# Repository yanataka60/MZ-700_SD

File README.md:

# MZ-700バンク切替対応MZ-80K_SD基板

　MZ-80K_SDはROMをF000Hに置くことでFDコマンドを利用してフロッピーディスク装置の代わりにSD-CARDを繋いでしまおうというものですが、MZ-700でバンク切替によりオールRAMとなったときに、MZ-80K_SDのROMがEnableのままなのでMZ-700本体のRAMと両方有効になってしまっています。

　実際にS-BASIC等動かしてみるとそのまま問題なく動いているようにも見えるのですが、バンクが切り替わったときにはROMがDisableになったほうが安心です。

　MZ-700_SDではバンクが切り替わったときにGAL16V8を使ってROMのDisable、Enableが自動で切り替わります。

#### 試作から2か月経過しましたが、特に問題が発生していないので正式公開とします。

~~####  ただし、MZ-80K_SD開発時に使っていたGAL22V10がMZ-80K本体と相性が悪いのかどうにも動作が不安定で泣く泣く汎用ロジックICに置き換えた経験からGALを使っても動作が安定していると確信できるまではテスト公開とします。~~

####  また、入手性も汎用ロジックICに比べてGAL16V8は良くないです。

　なお、GAL16V8、Arduino、ROMへ書き込むための機器が別途必要となります。

#### 2024.10.10 MZ-80K_SD基板をRev1.5.5とし、ROMを切り離しスイッチを標準装備としました。

　MZ-80K_SDのページではスイッチでROMを切り離すMZ-80K_SD Rev1.5.5基板を公開しています。

https://github.com/yanataka60/MZ80K_SD

　Rev1.5.3基板でROMを切り離すスイッチを付ける方法はこちらです。

https://github.com/yanataka60/MZ80K_SD?tab=readme-ov-file#rom%E5%88%87%E3%82%8A%E9%9B%A2%E3%81%97%E3%82%B9%E3%82%A4%E3%83%83%E3%83%81%E6%94%B9%E9%80%A0

### (2026.8.13追記)すねいるさんのBARYONに対応するためArduinoプログラムを更新しました。また、ROMプログラムも合わせて更新することで多段ロードにも対応します。

### 多段ロードの詳細についてはMZ-80K_SDの「BARYON対応」「多段ロード対応」を参照してください。

BARYON対応:https://github.com/yanataka60/MZ80K_SD#baryon%E5%AF%BE%E5%BF%9C2026813

多段ロード対応:https://github.com/yanataka60/MZ80K_SD#%E5%A4%9A%E6%AE%B5%E3%83%AD%E3%83%BC%E3%83%89%E5%AF%BE%E5%BF%9C2026813

　Arduinoプログラム、ROMプログラムともMZ-80K_SD用に更新したものがそのまま使えます。

## 回路図
　KiCadフォルダ内のMZ-700_SD.pdf参照

[回路図](https://github.com/yanataka60/MZ-700_SD/blob/main/KiCad/MZ700_SD.pdf)

## 部品
　U7 GAL16V8 1個が追加された以外はMZ-80K_SD Rev1.5.3と同様です。

　MZ-80K_SD Rev1.5.5との違いはRev1.5.5でのS3スイッチと10kΩの抵抗の代わりにGAL16V8が必要となります。

　私はGAL16V8Dを使っています。

|番号|品名|数量|備考|
| ------------ | ------------ | ------------ | ------------ |
|U1|74LS04|1||
|U2|2764又は28C64|1|ROMの相性については後述|
|U3|8255|1||
|U4|Arduino_Pro_Mini_5V|1|Atmega328版を使用 168版は不可。(注1)|
|U5 U6|74LS30|2||
|U7|GAL16V8|1||
||J2、J5のいづれか|||
|J2|Micro SD Card Kit又は同等品|1|秋月電子通商 AE-microSD-LLCNV (注2) (注3)|
|J5|MicroSD Card Adapter|1|Arduino等に使われる5V電源に対応したもの (注3)|
|C1-C5,C7|積層セラミックコンデンサ 0.1uF|6||
|C6|電解コンデンサ 16v100uF|1||
|S1 S2|3Pスライドスイッチ|2|秋月電子通商 SS12D01G4など|
|J4|DCジャック|1||
|J3|コネクタ 2Pin|1|ピンヘッダで代用するときはGNDと間違えないよう1Pinで5Vだけにしたほうが良い|
|J1|50Pinコネクタ|1||
||50Pinケーブル|1||
||ピンヘッダ|2Pin分|Arduino_Pro_MiniにはA4、A5用のピンヘッダが付いていないため別途調達が必要です 秋月電子通商 PH-1x40SGなど|
||本体内から5Vを取る場合、ケーブル少々|||
||本体ROMにパッチをあてる場合、27C32等を2532ソケットに差すためのアダプタ|||
||ピンソケット(任意)|26Pin分|Arduino_Pro_Miniを取り外し可能としたい場合に調達します 秋月電子通商 FHU-1x42SGなど|

　　　注1)Arduino Pro MiniはA4、A5ピンも使っています。

　　　注2)秋月電子通商　AE-microSD-LLCNVのJ1ジャンパはショートしてください。

　　　注3)J2又はJ5のどちらかを選択して取り付けてください。

### MicroSD Card Adapterを使う(Rev1.5.3以降)
J5に取り付けます。

MicroSD Card Adapterについているピンヘッダを除去してハンダ付けするのが一番確実ですが、J5の穴にMicroSD Card Adapterをぴったりと押しつけ、裏から多めにハンダを流し込むことでハンダ付けをする方法もあります。なお、この方法の時にはしっかりハンダ付けが出来たかテスターで導通を確認しておいた方が安心です。

ハンダ付けに自信のない方はJ2の秋月電子通商　AE-microSD-LLCNVをお使いください。AE-microSD-LLCNVならパワーLED、アクセスLEDが付いています。

.JPG)

.JPG)

.JPG)

.JPG)

## GAL16V8プログラム
　Wincuplフォルダ内のMZ700_ROM.jedをROMライター(TL866II Plus等)を使ってGAL16V8に書き込んでください。

## ROMプログラムについて、Arduinoプログラム等
　以下、MZ-80K_SD Rev1.5.5と同様ですのでMZ-80K_SDプロジェクトを参照してください。。

https://github.com/yanataka60/MZ80K_SD?tab=readme-ov-file#rom%E3%83%97%E3%83%AD%E3%82%B0%E3%83%A9%E3%83%A0%E3%81%AB%E3%81%A4%E3%81%84%E3%81%A6

## テストプログラム
　RAMへの書込みが正常に行われ、読み出す時にはROMのデータと混じらずに書き込んだデータと同じ値が正常に読み出せること、またROMを読み出してもデータが不変であることを確認するためにテストプログラムを作成しました。

　Z80フォルダTESTフォルダ内のTEST-MZ700.MZTを実行するとROMを読出して比較、RAMに書込み、読出して比較をバンク切替しながらF000hからFFFFhまでのメモリアドレスを順次検査していき、RAMの読出し比較がエラーとなればそこで止まります。

　私の環境でバンク切替対応基板が正常に終了することは確認済みですが、困ったことに未対策のMZ-80K_SD Rev1.5.3基板でも正常に終了してしまいました。

　MZ-80Kではスタートと同時にエラーで止まりますのでテストプログラムは正常なはずです。

　ROMとRAMのアクセスタイムが関係しているのかもしれませんが、バンク切替対応基板だとここが直りますというところが明確ではないです。

　なお、ロジックアナライザを使い、バンク切替対応基板ではOUT (E1h),AでGAL16V8 Pin17(LATCH)がDisableとなり、OUT (E3h),A、OUT (E4h),AでGAL16V8 Pin17(LATCH)がEnableとなり正常に動作することは確認しています。

　　未対策のMZ-80K_SD Rev1.5.3基板ではOUT (E1h),A、OUT (E3h),A、OUT (E4h),Aいずれの状態でもF000h～FFFFhアクセス時にROMCEはEnableのままです。

## EMMボード for MZ-700からの起動
　拙作EMMボード for MZ-700をバッテリーバックアップに対応させたのでEMM_for_MZ-700から起動するコマンドを追加してみました。

　https://github.com/yanataka60/EMM_for_MZ-700

　コマンド「FDE0」～「FDE3」を使うことで「EMM0」～「EMM3」のHuBASICから起動させることが出来ます。

　なお、EMMの00000番地が「01h」でなければEMMからの起動はせずにコマンド待ちに戻りますが、00000番地以降に異常があってもチェックはしていないので最悪暴走します。

　MZ-700用HuBASICはテープ版しかなくそのままではEMMにHuBASICの起動イメージを作成することが出来ません。

　BouKiCHiさんのHuDiskなどを使いMZ-700用HuBASICの起動ディスクイメージを作成したうえでEMMMENUのEMMLOADでEMMに書き込む必要があります。

### ROMに書き込む
~~EMMフォルダ内のFD_rom.BINをROMライター(TL866II Plus等)を使って2764に書き込んでください。~~

(2026.8.13)多段ロード対応に伴い、MZ-80K_SDに統合しました。MZ-80K_SD/Z80フォルダ内のFD_rom.BINを使ってください。

## 謝辞
　基板の作成に当たり以下のデータを使わせていただきました。ありがとうございました。

　Arduino Pro Mini

　　https://github.com/g200kg/kicad-lib-arduino

　AE-microSD-LLCNV

　　https://github.com/kuninet/PC-8001-SD-8kRAM

## 追記
2024.10.10 正式公開

2025.12.4 kuran_kuranさんにArduinoプログラムのバグを発見していただきました。精査した結果、不要な処理が含まれていることが原因であったため不要な処理部分を削除しました。なお、未修正のままでも実害はありません。kuran_kuranさん、ありがとうございました。

2026.1.23 EMMサポートプログラムを追加。

2026.8.13 BARYONに対応しました。retrogamer128さんの要望により多段ロードに対応しました。

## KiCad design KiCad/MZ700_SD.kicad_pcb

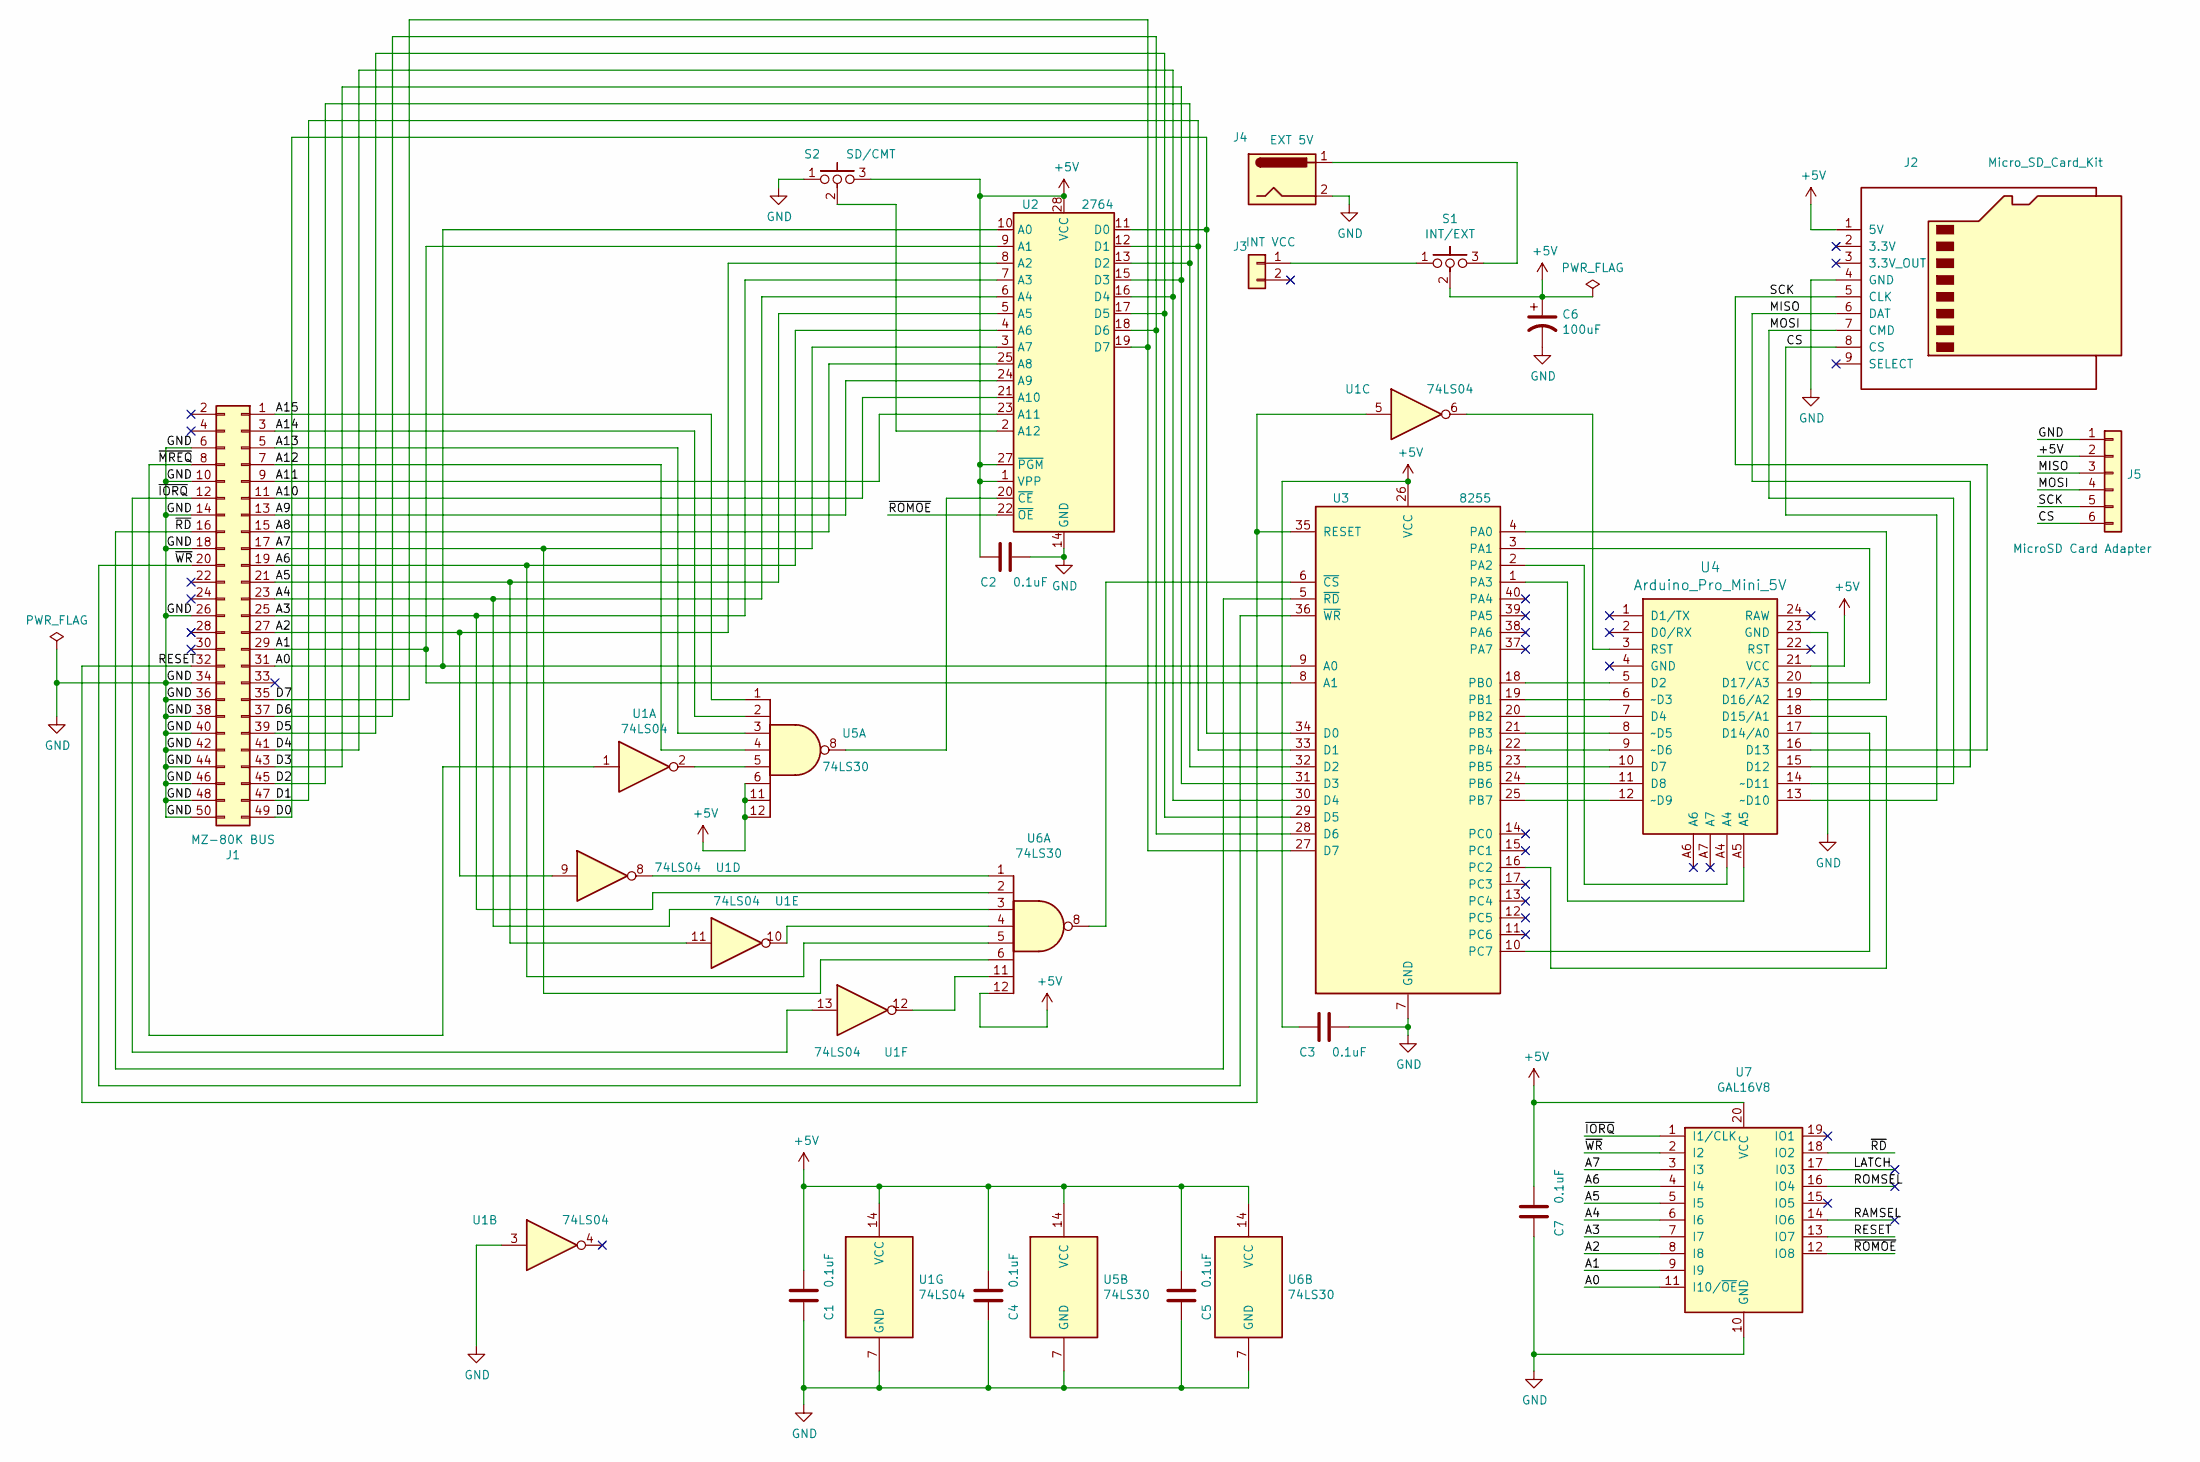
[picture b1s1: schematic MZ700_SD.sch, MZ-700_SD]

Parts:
C1, C2, C3, C4, C5, C7: 0.1uF; C_Rect_L4.0mm_W2.5mm_P2.50mm
C6: 100uF; CP_Radial_D5.0mm_P2.50mm
J1: MZ-80K BUS; PinSocket_2x25_P2.54mm_Horizontal
J2: Micro_SD_Card_Kit; AE-microSD-LLCNV
J3: INT VCC; PinHeader_1x02_P2.54mm_Horizontal
J4: EXT 5V; BarrelJack_Horizontal
J5: MicroSD Card Adapter; PinSocket_1x06_P2.54mm_Vertical
S1: INT/EXT; PinHeader_1x03_P2.54mm_Vertical
S2: SD/CMT; PinHeader_1x03_P2.54mm_Vertical
U1: 74LS04; DIP-14_W7.62mm_LongPads
U2: 2764; DIP-28_W15.24mm_LongPads
U3: 8255; DIP-40_W15.24mm_LongPads
U4: Arduino_Pro_Mini_5V; Arduino_Pro_Mini
U5, U6: 74LS30; DIP-14_W7.62mm_LongPads
U7: GAL16V8; DIP-20_W7.62mm_LongPads

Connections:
+5V: C1.2, C2.1, C3.1, C4.2, C5.2, C6.1, C7.2, J2.1 (5V), J5.2, S1.2, S2.3, U1.14 (VCC), U2.1 (VPP), U2.27 (~PGM), U2.28 (VCC), U3.26 (VCC), U4.21 (VCC), U5.6, U5.11, U5.12, U5.14 (VCC), U6.12, U6.14 (VCC), U7.20 (VCC)
/A0: J1.31, U2.10 (A0), U3.9 (A0), U7.11 (I10/~OE~)
/A1: J1.29, U2.9 (A1), U3.8 (A1), U7.9 (I9)
/A2: J1.27, U1.9, U2.8 (A2), U7.8 (I8)
/A3: J1.25, U2.7 (A3), U6.2, U7.7 (I7)
/A4: J1.23, U2.6 (A4), U6.3, U7.6 (I6)
/A5: J1.21, U1.11, U2.5 (A5), U7.5 (I5)
/A6: J1.19, U2.4 (A6), U6.5, U7.4 (I4)
/A7: J1.17, U2.3 (A7), U6.6, U7.3 (I3)
/A8: J1.15, U2.25 (A8)
/A9: J1.13, U2.24 (A9)
/A10: J1.11, U2.21 (A10)
/A11: J1.9, U2.23 (A11)
/A12: J1.7, U5.4
/A13: J1.5, U5.3
/A14: J1.3, U5.2
/A15: J1.1, U5.1
/CS: J2.8 (CS), J5.6, U4.13 (~~D10)
/D0: J1.49, U2.11 (D0), U3.34 (D0)
/D1: J1.47, U2.12 (D1), U3.33 (D1)
/D2: J1.45, U2.13 (D2), U3.32 (D2)
/D3: J1.43, U2.15 (D3), U3.31 (D3)
/D4: J1.41, U2.16 (D4), U3.30 (D4)
/D5: J1.39, U2.17 (D5), U3.29 (D5)
/D6: J1.37, U2.18 (D6), U3.28 (D6)
/D7: J1.35, U2.19 (D7), U3.27 (D7)
/MISO: J2.6 (DAT), J5.3, U4.15 (D12)
/MOSI: J2.7 (CMD), J5.4, U4.14 (~~D11)
/RESET: J1.32, U1.5, U3.35 (RESET), U7.13 (IO7)
/SCK: J2.5 (CLK), J5.5, U4.16 (D13)
/~IORQ: J1.12, U1.13, U7.1 (I1/CLK)
/~MREQ: J1.8, U1.1
/~RD: J1.16, U3.5 (~RD~), U7.18 (IO2)
/~ROMOE: U2.22 (~OE), U7.12 (IO8)
/~WR: J1.20, U3.36 (~WR~), U7.2 (I2)
GND: C1.1, C2.2, C3.2, C4.1, C5.1, C6.2, C7.1, J1.6, J1.10, J1.14, J1.18, J1.26, J1.34, J1.36, J1.38, J1.40, J1.42, J1.44, J1.46, J1.48, J1.50, J2.4 (GND), J4.2, J5.1, S2.1, U1.3, U1.7 (GND), U2.14 (GND), U3.7 (GND), U4.23 (GND), U5.7 (GND), U6.7 (GND), U7.10 (GND)
unnamed: J3.1, S1.1
unnamed: J4.1, S1.3
unnamed: S2.2, U2.2 (A12)
unnamed: U1.2, U5.5
unnamed: U1.6, U4.3 (RST)
unnamed: U1.8, U6.1
unnamed: U1.10, U6.4
unnamed: U1.12, U6.11
unnamed: U2.20 (~CE), U5.8
unnamed: U3.1 (PA3), U4.A5
unnamed: U3.2 (PA2), U4.A4
unnamed: U3.3 (PA1), U4.20 (D17/A3)
unnamed: U3.4 (PA0), U4.19 (D16/A2)
unnamed: U3.6 (~CS~), U6.8
unnamed: U3.10 (PC7), U4.17 (D14/A0)
unnamed: U3.16 (PC2), U4.18 (D15/A1)
unnamed: U3.18 (PB0), U4.5 (D2)
unnamed: U3.19 (PB1), U4.6 (~~D3)
unnamed: U3.20 (PB2), U4.7 (D4)
unnamed: U3.21 (PB3), U4.8 (~~D5)
unnamed: U3.22 (PB4), U4.9 (~~D6)
unnamed: U3.23 (PB5), U4.10 (D7)
unnamed: U3.24 (PB6), U4.11 (D8)
unnamed: U3.25 (PB7), U4.12 (~~D9)

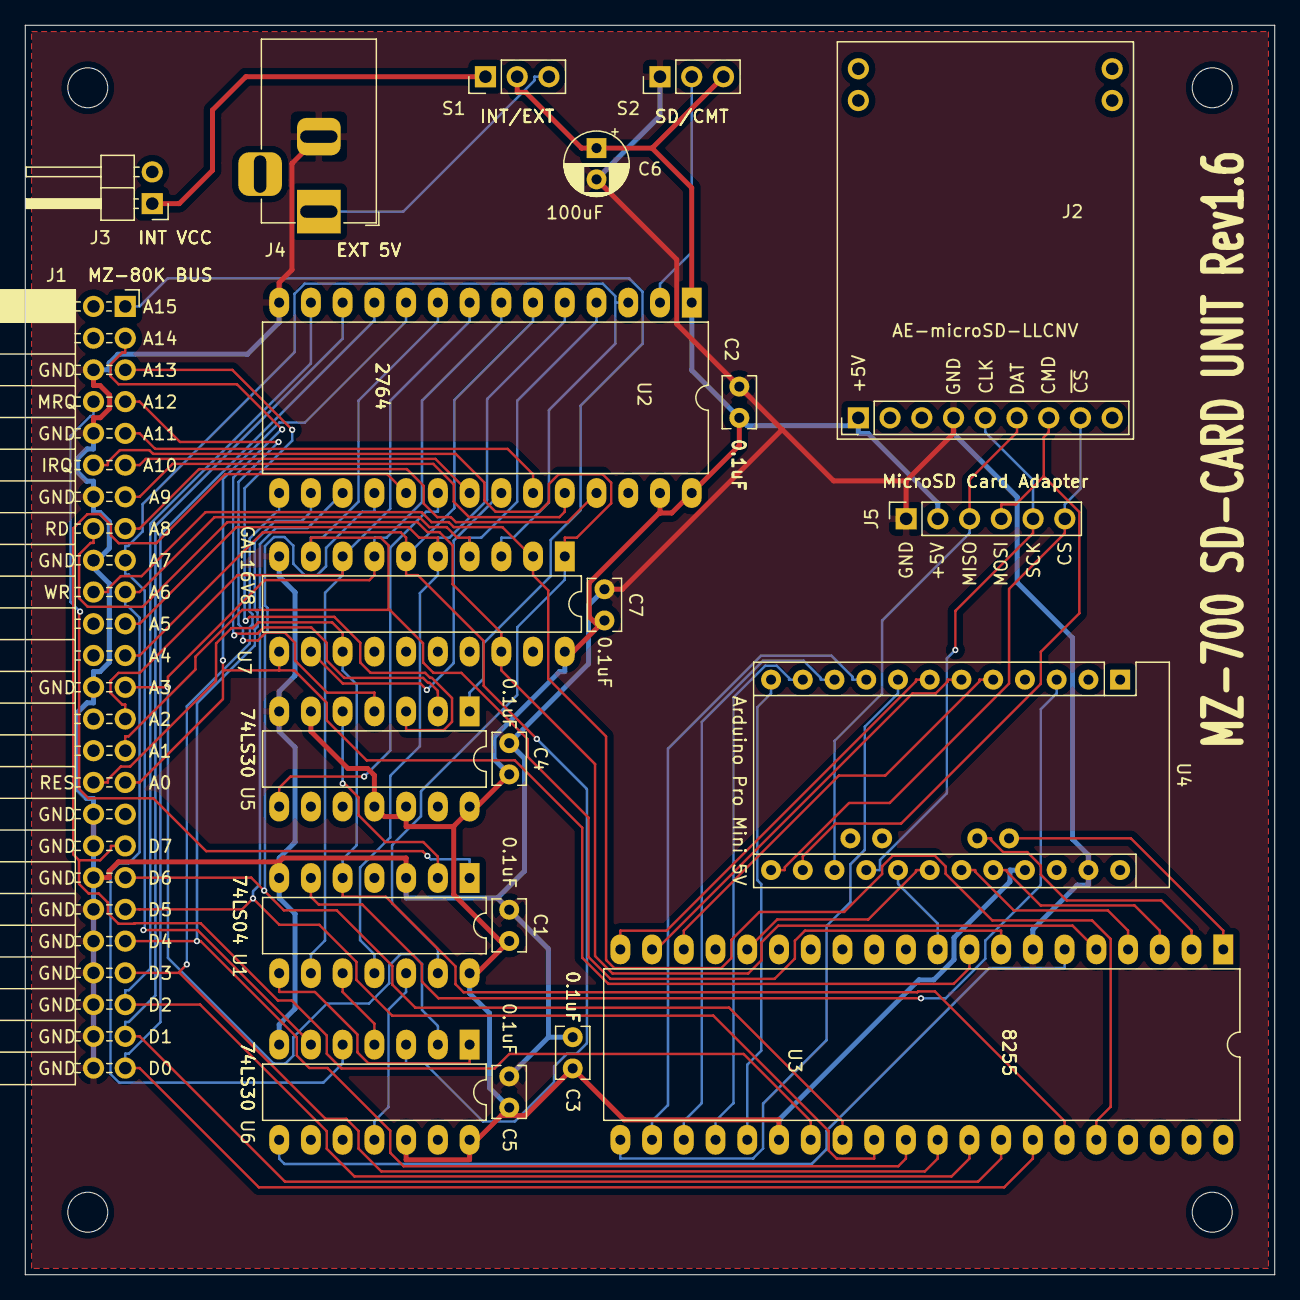
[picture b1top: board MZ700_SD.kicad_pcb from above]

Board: 2 copper layers, 100.0 x 100.0 mm, 25 parts (0 on the bottom side), 60 nets.

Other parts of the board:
MH1, MH2, MH3, MH4: MountingHole_3.2mm_M3
